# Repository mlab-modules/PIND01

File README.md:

# PIND01 -  PIN diode array of photodiodes for dosimeter

The module includes multiple of parallel connected  photo-diodes for PIN based dosimeter.

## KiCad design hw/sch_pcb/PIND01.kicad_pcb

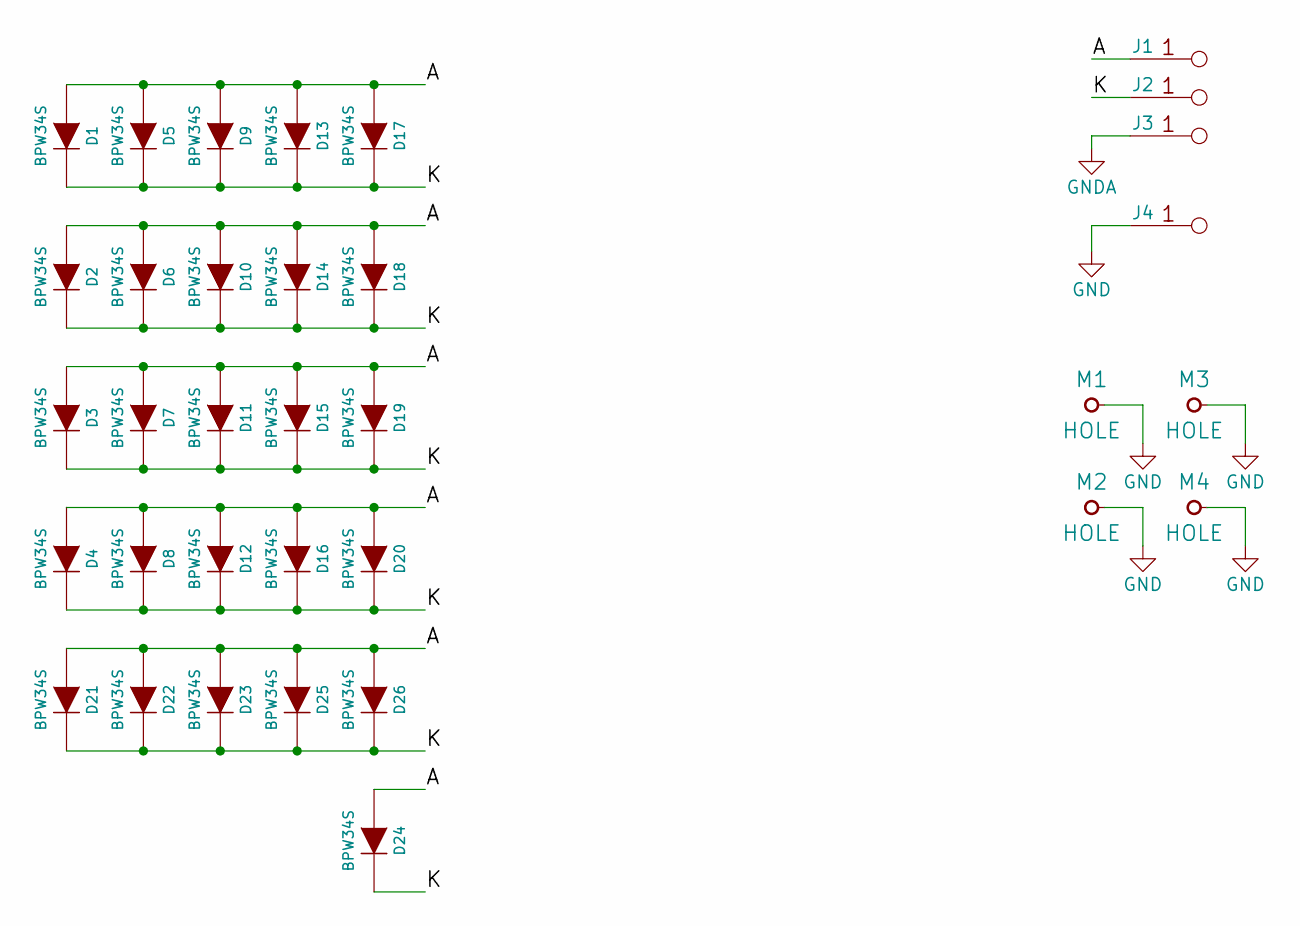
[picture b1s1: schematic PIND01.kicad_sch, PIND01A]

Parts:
D1, D2, D3, D4, D5, D6, D7, D8, D9, D10, D11, D12, D13, D14, D15, D16, D17, D18, D19, D20, D21, D22, D23, D24, D25, D26: BPW34S; DIL
J1, J2, J3, J4: JUMP_2x1; Straight_2x01
M1, M2, M3, M4: HOLE; MountingHole_3mm

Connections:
/A: D1.2 (A), D2.2 (A), D3.2 (A), D4.2 (A), D5.2 (A), D6.2 (A), D7.2 (A), D8.2 (A), D9.2 (A), D10.2 (A), D11.2 (A), D12.2 (A), D13.2 (A), D14.2 (A), D15.2 (A), D16.2 (A), D17.2 (A), D18.2 (A), D19.2 (A), D20.2 (A), D21.2 (A), D22.2 (A), D23.2 (A), D24.2 (A), D25.2 (A), D26.2 (A), J1.1, J1.2
/K: D1.1 (K), D2.1 (K), D3.1 (K), D4.1 (K), D5.1 (K), D6.1 (K), D7.1 (K), D8.1 (K), D9.1 (K), D10.1 (K), D11.1 (K), D12.1 (K), D13.1 (K), D14.1 (K), D15.1 (K), D16.1 (K), D17.1 (K), D18.1 (K), D19.1 (K), D20.1 (K), D21.1 (K), D22.1 (K), D23.1 (K), D24.1 (K), D25.1 (K), D26.1 (K), J2.1, J2.2
GND: J4.1, J4.2, M1.1, M2.1, M3.1, M4.1
GNDA: J3.1, J3.2

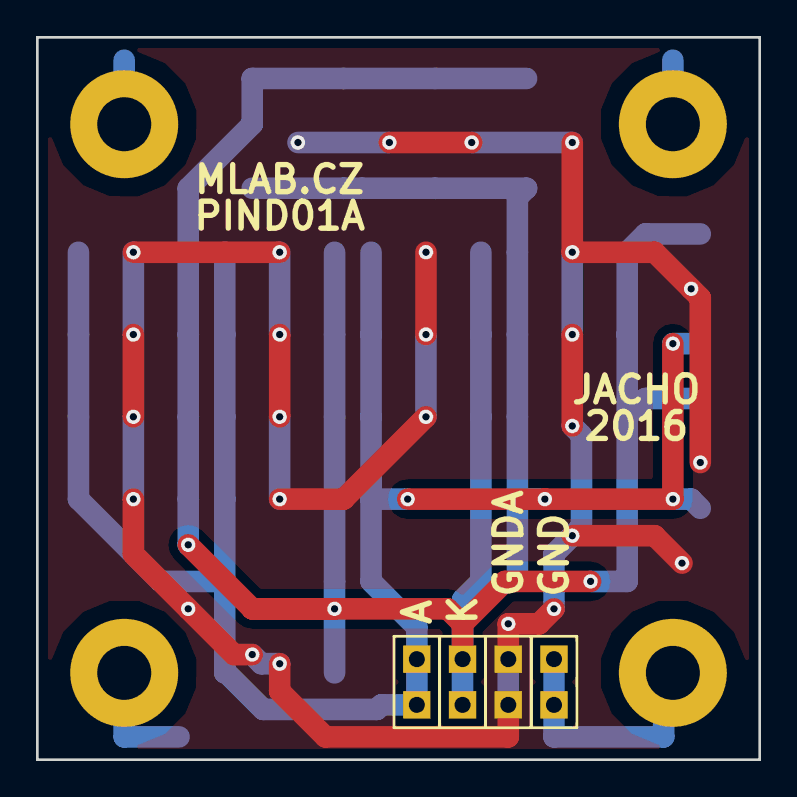
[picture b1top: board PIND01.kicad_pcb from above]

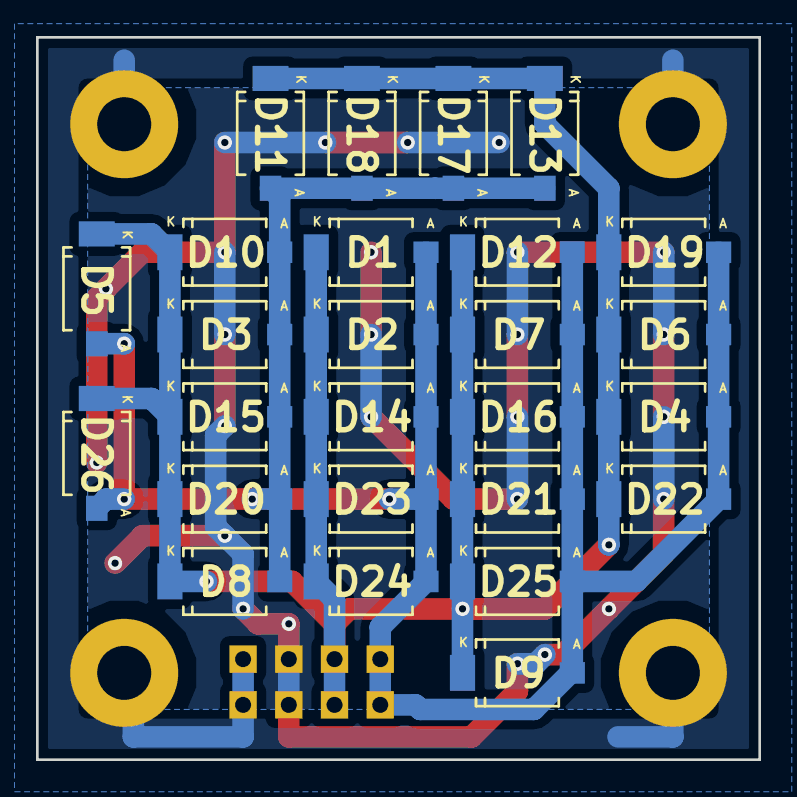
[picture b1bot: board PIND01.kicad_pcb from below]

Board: 2 copper layers, 40.1 x 40.1 mm, 34 parts (26 on the bottom side), 4 nets.

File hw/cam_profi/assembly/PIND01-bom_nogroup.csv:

Component,Description,Part,References,Value,Footprint,Quantity Per PCB,Datasheet
1,,DIODE,D1D2D3D4D5D6D7D8D9D10D11D12D13D14D15D16D17D18D19D20D21D22D23D24D25D26,BPW34S,DIL,26,
2,,JUMP_2x1,J1J2J3J4,JUMP_2x1,Straight_2x01,4,

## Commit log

2023-04-01 Adding force option to enable splitting in not fresh copy of Modules repository.
2023-05-28 automated commit; add github actions
2023-05-28 Update workflow files
2023-05-28 Update metadata files
2023-07-05 automated commit; rename source files to new naming convence
2023-09-16 Update status
2024-07-04 Update Project to KiCADv7.
2024-07-04 Update actions products
2024-07-04 Update documentation.
